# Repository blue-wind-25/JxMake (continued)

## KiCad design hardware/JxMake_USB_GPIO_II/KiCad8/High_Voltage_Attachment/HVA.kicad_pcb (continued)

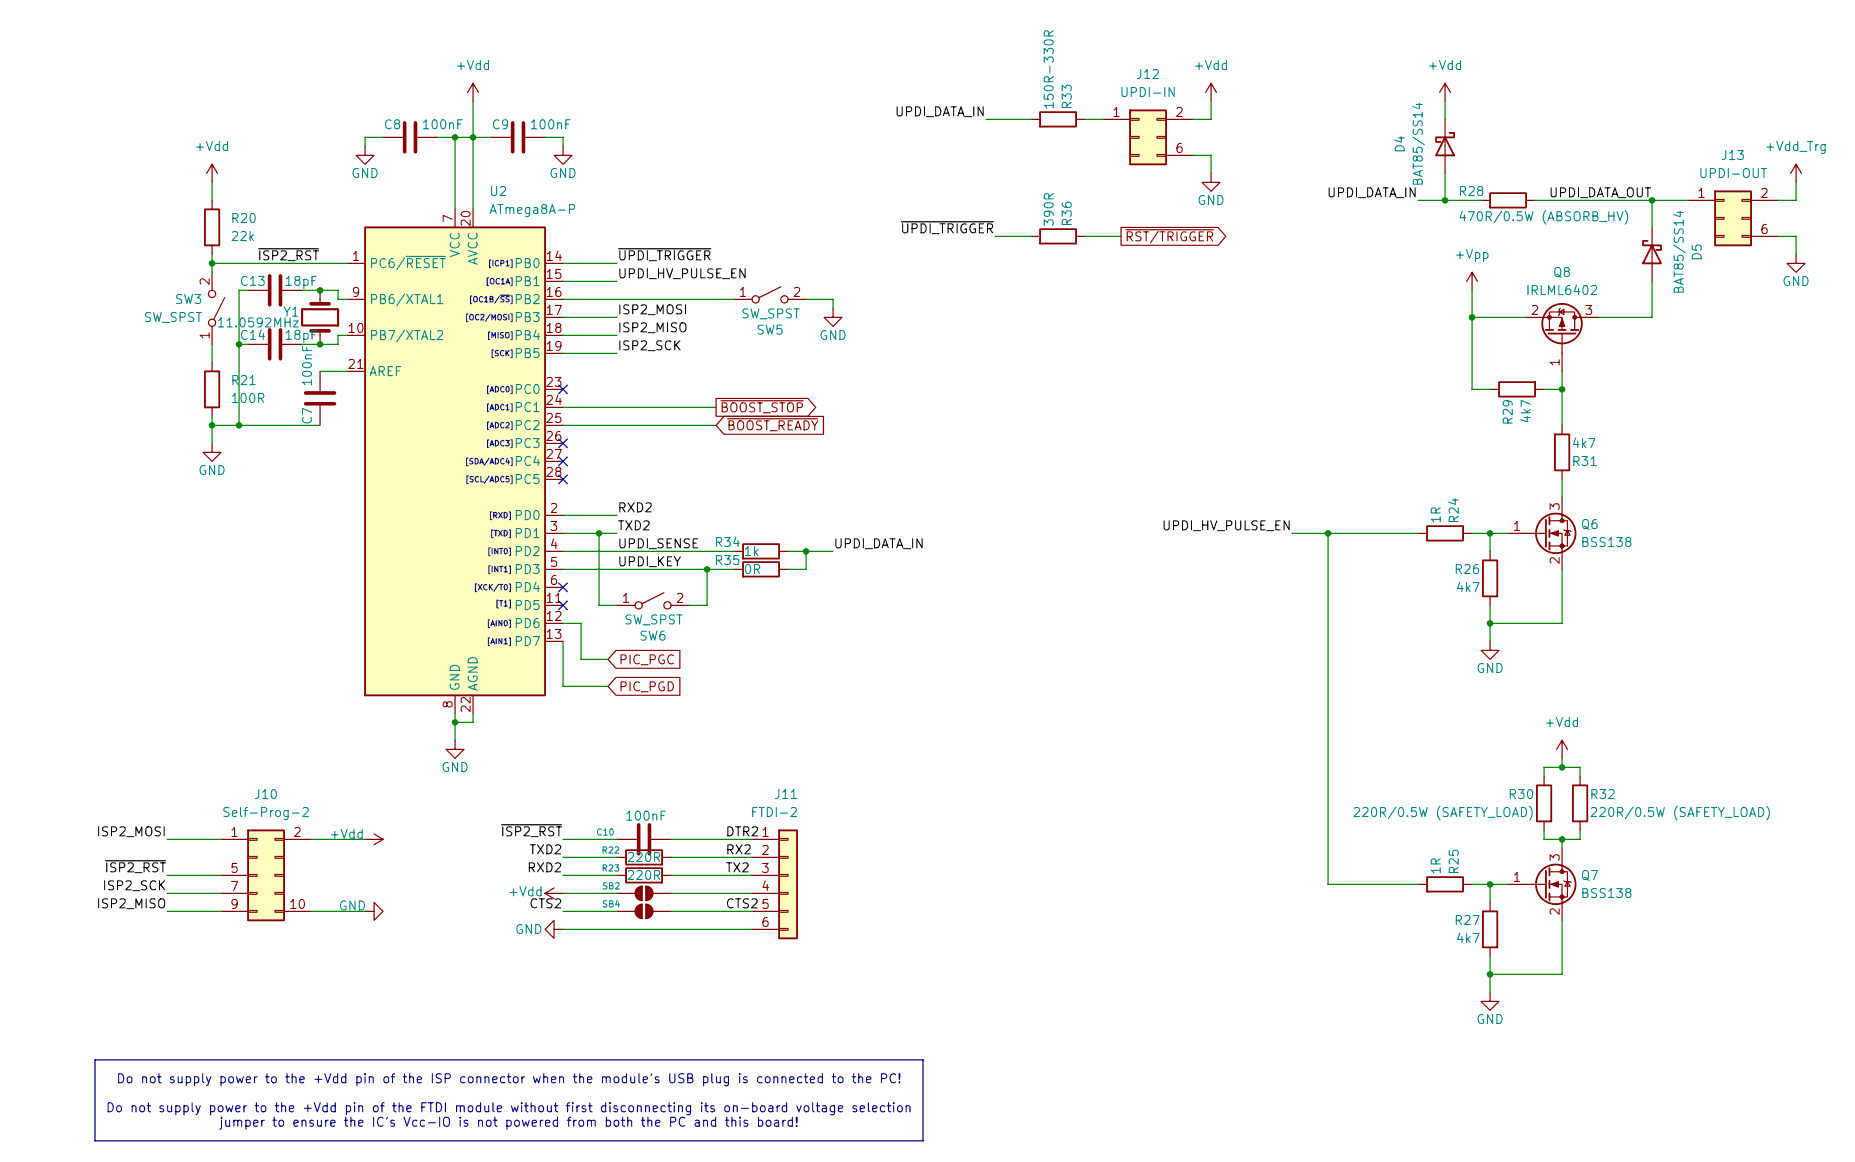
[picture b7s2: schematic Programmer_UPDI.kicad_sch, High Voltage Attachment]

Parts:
C7, C8, C9, C10: 100nF; C_0805_2012Metric_Pad1.18x1.45mm_HandSolder
C13, C14: 18pF; C_0805_2012Metric_Pad1.18x1.45mm_HandSolder
D4, D5: BAT85/SS14; D_SMA
J10: Self-Prog-2; IDC-Header_2x05_P2.54mm_Vertical
J11: FTDI-2; PinSocket_1x06_P2.54mm_Horizontal
J12: UPDI-IN; IDC-Header_2x03_P2.54mm_Vertical
J13: UPDI-OUT; IDC-Header_2x03_P2.54mm_Vertical
Q6, Q7: BSS138; SOT-23_Handsoldering
Q8: IRLML6402; SOT-23_Handsoldering
R20: 22k; R_0805_2012Metric_Pad1.20x1.40mm_HandSolder
R21: 100R; R_0805_2012Metric_Pad1.20x1.40mm_HandSolder
R22, R23: 220R; R_0805_2012Metric_Pad1.20x1.40mm_HandSolder
R24, R25: 1R; R_0805_2012Metric_Pad1.20x1.40mm_HandSolder
R26, R27, R29, R31: 4k7; R_0805_2012Metric_Pad1.20x1.40mm_HandSolder
R28: 470R/0.5W (ABSORB_HV); R_Axial_DIN0207_L6.3mm_D2.5mm_P10.16mm_Horizontal
R30, R32: 220R/0.5W (SAFETY_LOAD); R_Axial_DIN0207_L6.3mm_D2.5mm_P10.16mm_Horizontal
R33: 150R-330R; R_0805_2012Metric_Pad1.20x1.40mm_HandSolder
R34: 1k; R_0805_2012Metric_Pad1.20x1.40mm_HandSolder
R35: 0R; R_0805_2012Metric_Pad1.20x1.40mm_HandSolder
R36: 390R; R_0805_2012Metric_Pad1.20x1.40mm_HandSolder
SB2, SB4: Jumper_2_Small_Bridged; SolderJumper-2_P1.3mm_Open_RoundedPad1.0x1.5mm
SW3, SW5: SW_SPST; SW_SPST_FSMSM
SW6: SW_SPST; PinHeader_1x02_P2.54mm_Vertical
U2: ATmega8A-P; DIP-28_W7.62mm
Y1: 11.0592MHz; Crystal_SMD_HC49-SD

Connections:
+Vdd: C8.2, C9.1, D4.1 (K), J10.2, J12.2, R20.1, R30.1, R32.1, SB2.1 (A), U2.7 (VCC), U2.20 (AVCC); also elsewhere on the board
+Vdd_Trg: J13.2; also elsewhere on the board
+Vpp: Q8.2 (S), R29.1; also elsewhere on the board
/Programmer_UPDI/CTS2: J11.5, SB4.1 (A), SB4.2 (B)
/Programmer_UPDI/DTR2: C10.2, J11.1
/Programmer_UPDI/ISP2_MISO: J10.9, U2.18 (PB4)
/Programmer_UPDI/ISP2_MOSI: J10.1, U2.17 (PB3)
/Programmer_UPDI/ISP2_SCK: J10.7, U2.19 (PB5)
/Programmer_UPDI/RX2: J11.2, R22.2
/Programmer_UPDI/RXD2: R23.1, U2.2 (PD0)
/Programmer_UPDI/TX2: J11.3, R23.2
/Programmer_UPDI/TXD2: R22.1, SW6.1 (A), U2.3 (PD1)
/Programmer_UPDI/UPDI_DATA_IN: D4.2 (A), R28.2, R33.2, R34.1, R35.1
/Programmer_UPDI/UPDI_DATA_OUT: D5.1 (K), J13.1, R28.1
/Programmer_UPDI/UPDI_HV_PULSE_EN: R24.2, R25.2, U2.15 (PB1)
/Programmer_UPDI/UPDI_KEY: R35.2, SW6.2 (B), U2.5 (PD3)
/Programmer_UPDI/UPDI_SENSE: R34.2, U2.4 (PD2)
/Programmer_UPDI/~ISP2_RST: C10.1, J10.5, R20.2, SW3.2 (B), U2.1 (PC6/~RESET)
/Programmer_UPDI/~UPDI_TRIGGER: R36.2, U2.14 (PB0)
GND: C7.1, C8.1, C9.2, C13.1, C14.1, J10.10, J11.6, J12.6, J13.6, Q6.2 (S), Q7.2 (S), R21.2, R26.2, R27.2, SW5.2 (B), U2.8 (GND), U2.22 (AGND); also elsewhere on the board
unnamed: D5.2 (A), Q8.3 (D)
unnamed: J11.4, SB2.2 (B)
unnamed: J12.1, R33.1
unnamed: Q6.3 (D), R31.1
unnamed: Q6.1 (G), R24.1, R26.1
unnamed: Q7.3 (D), R30.2, R32.2
unnamed: Q7.1 (G), R25.1, R27.1
unnamed: Q8.1 (G), R29.2, R31.2
unnamed: R21.1, SW3.1 (A)
unnamed: SW5.1 (A), U2.16 (PB2)
unnamed: C7.2, U2.21 (AREF)
unnamed: C13.2, U2.9 (PB6/XTAL1), Y1.2
unnamed: C14.2, U2.10 (PB7/XTAL2), Y1.1
PIC_PGC: U2.12 (PD6); also elsewhere on the board
PIC_PGD: U2.13 (PD7); also elsewhere on the board
~BOOST_READY: U2.25 (PC2); also elsewhere on the board
~BOOST_STOP: U2.24 (PC1); also elsewhere on the board
~RST/TRIGGER: R36.1; also elsewhere on the board

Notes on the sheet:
Do not supply power to the +Vdd pin of the ISP connector when the module's USB plug is connected to the PC! Do not supply power to the +Vdd pin of the FTDI module without first disconnecting its on-board voltage selection jumper to ensure the IC's Vcc-IO is not powered from both the PC and this boa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
[OC2/MOSI]
[SCL/ADC5]
[XCK/T0]
[INT0]
[ADC1]
[T1]
[RXD]
[ADC2]
[AIN1]
[INT1]
[AIN0]
[TXD]
[MISO]
[SCK]
[ADC0]
[SDA/ADC4]
[ICP1]
[OC1B/~{SS}]
[OC1A]
[ADC3]

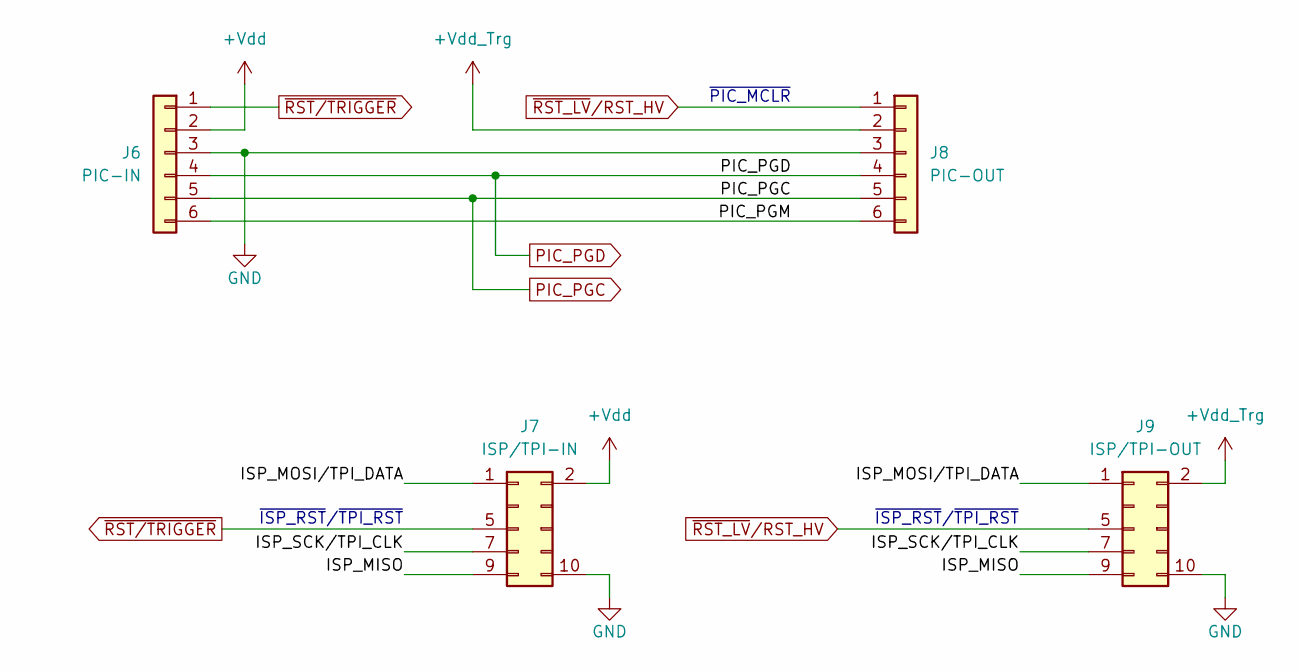
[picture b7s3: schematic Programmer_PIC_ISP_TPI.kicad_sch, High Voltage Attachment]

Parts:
J6: PIC-IN; PinSocket_1x06_P2.54mm_Horizontal
J7: ISP/TPI-IN; IDC-Header_2x05_P2.54mm_Vertical
J8: PIC-OUT; PinSocket_1x06_P2.54mm_Horizontal
J9: ISP/TPI-OUT; IDC-Header_2x05_P2.54mm_Vertical

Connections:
+Vdd: J6.2, J7.2; also elsewhere on the board
+Vdd_Trg: J8.2, J9.2; also elsewhere on the board
/Programmer_PIC_ISP_TPI/ISP_MISO: J7.9, J9.9
/Programmer_PIC_ISP_TPI/ISP_MOSI/TPI_DATA: J7.1, J9.1
/Programmer_PIC_ISP_TPI/ISP_SCK/TPI_CLK: J7.7, J9.7
/Programmer_PIC_ISP_TPI/PIC_PGM: J6.6, J8.6
GND: J6.3, J7.10, J8.3, J9.10; also elsewhere on the board
PIC_PGC: J6.5, J8.5; also elsewhere on the board
PIC_PGD: J6.4, J8.4; also elsewhere on the board
~RST_LV/RST_HV: J8.1, J9.5; also elsewhere on the board
~RST/TRIGGER: J6.1, J7.5; also elsewhere on the board

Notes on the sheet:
~{ISP_RST}/~{TPI_RST}
~{PIC_MCLR}

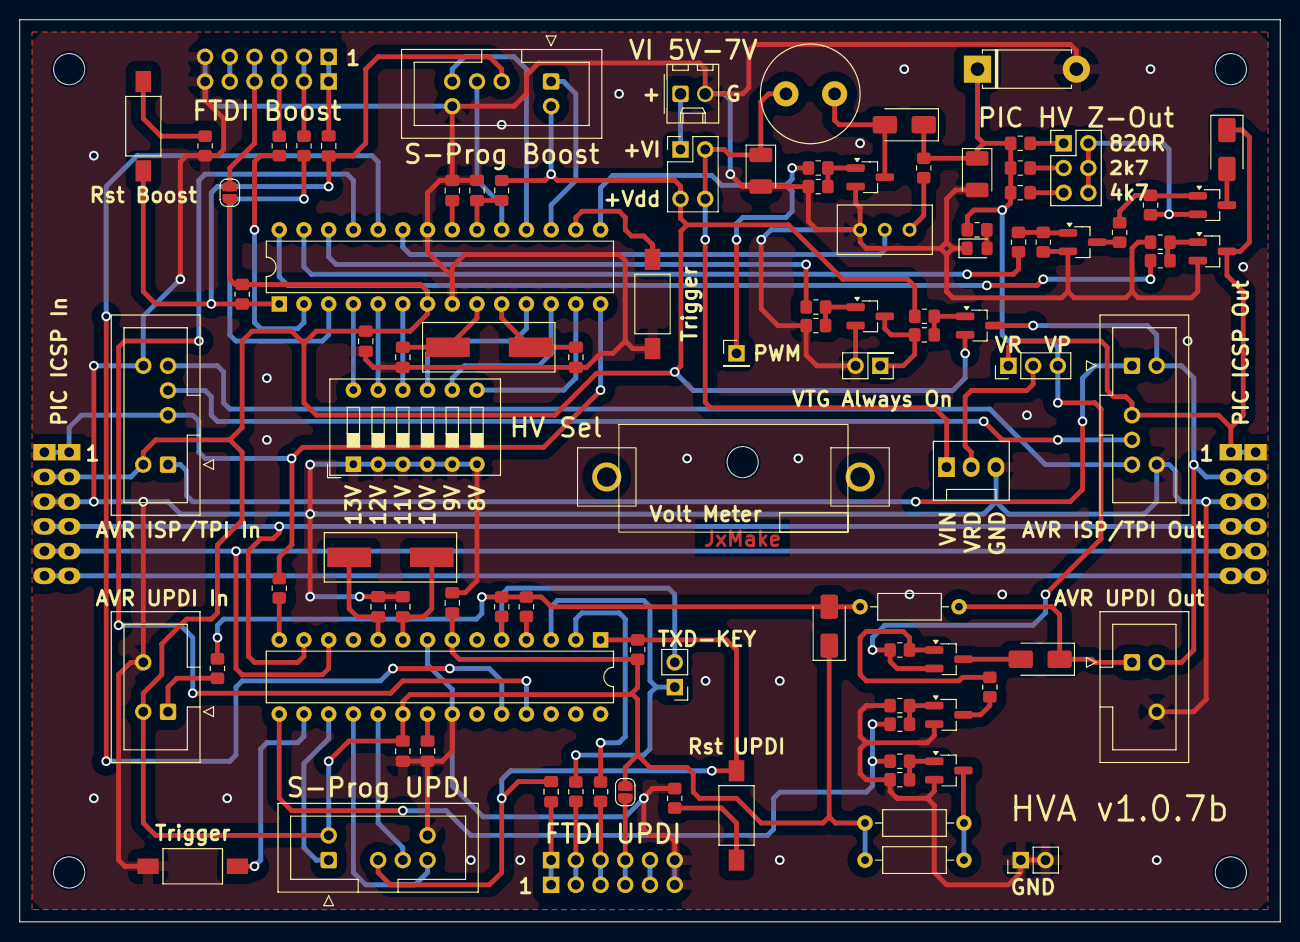
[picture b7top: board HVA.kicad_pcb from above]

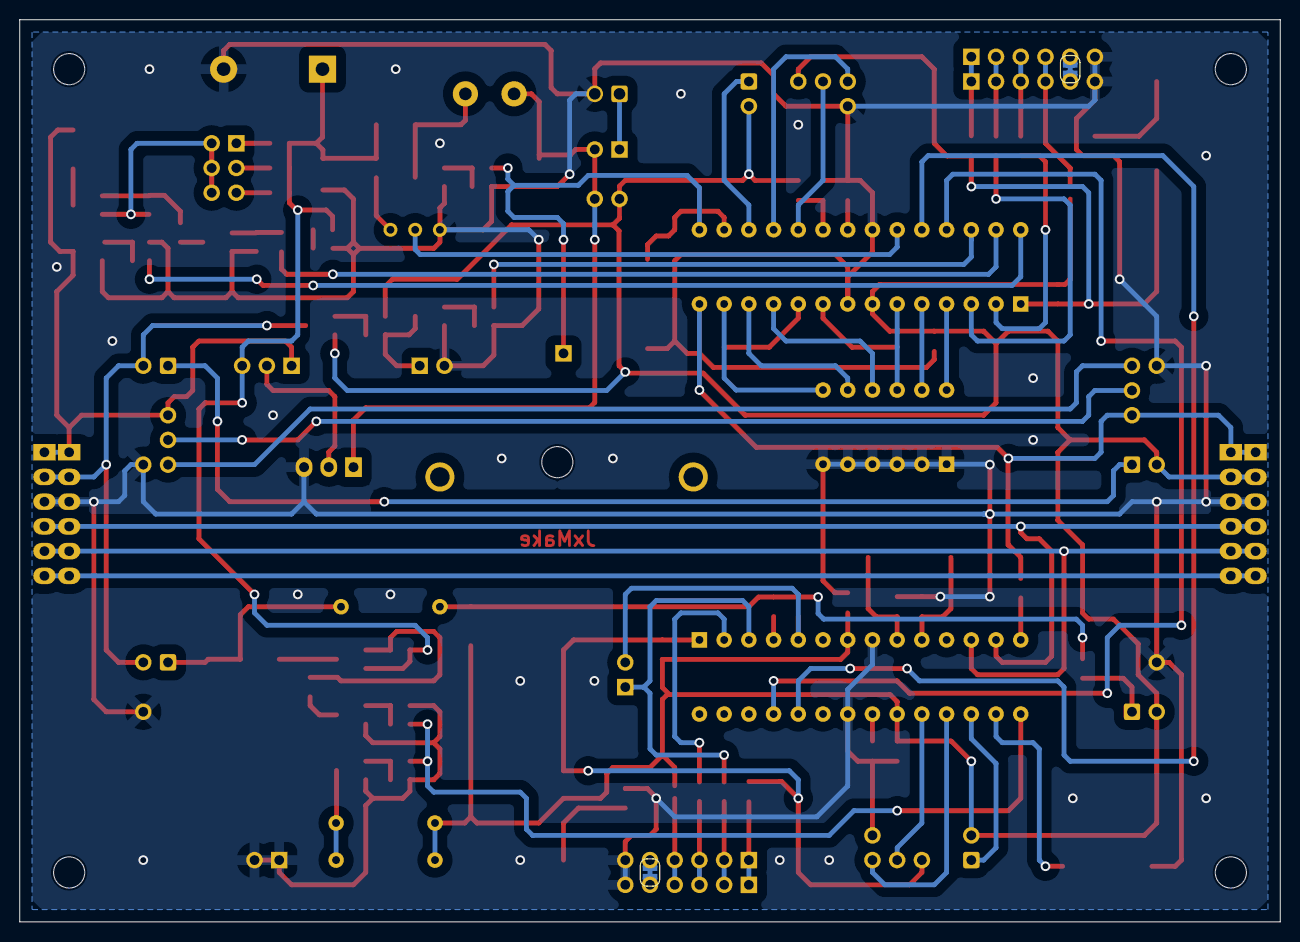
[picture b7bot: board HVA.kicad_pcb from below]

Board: 2 copper layers, 129.5 x 92.7 mm, 107 parts (2 on the bottom side), 90 nets.

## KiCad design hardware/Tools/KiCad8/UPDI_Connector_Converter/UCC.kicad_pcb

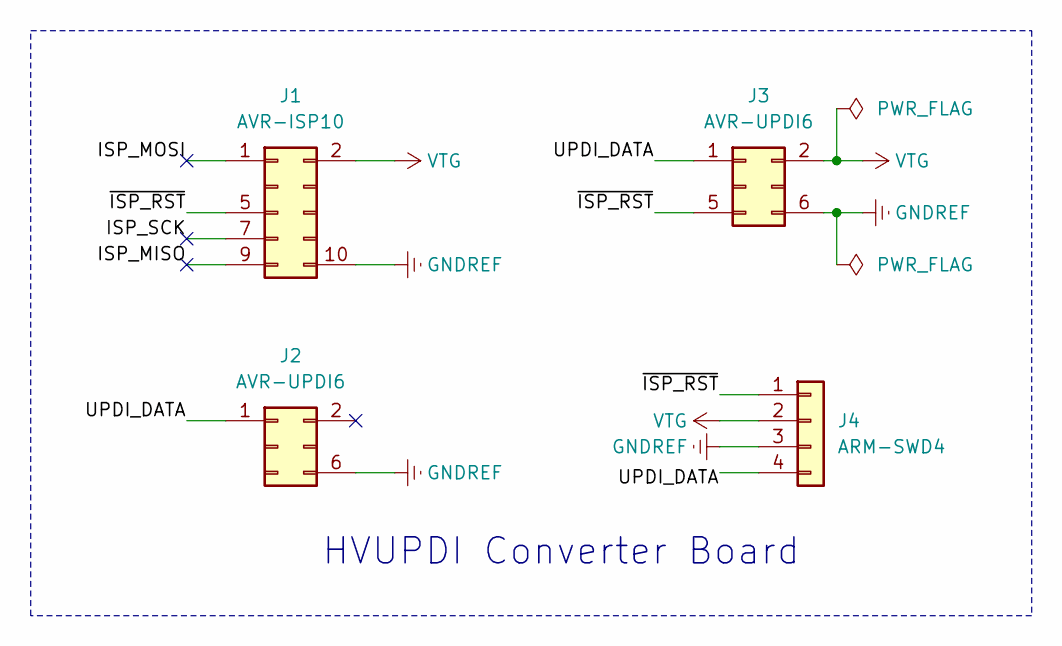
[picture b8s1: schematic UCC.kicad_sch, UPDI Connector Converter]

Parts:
J1: AVR-ISP10; IDC-Header_2x05_P2.54mm_Vertical
J2, J3: AVR-UPDI6; IDC-Header_2x03_P2.54mm_Vertical
J4: ARM-SWD4; PinSocket_1x04_P2.54mm_Horizontal

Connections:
/ISP_MISO: J1.9
/ISP_MOSI: J1.1
/ISP_SCK: J1.7
/UPDI_DATA: J2.1, J3.1, J4.4
/~ISP_RST: J1.5, J3.5, J4.1
GNDREF: J1.10, J2.6, J3.6, J4.3
VTG: J1.2, J3.2, J4.2

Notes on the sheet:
HVUPDI Converter Board

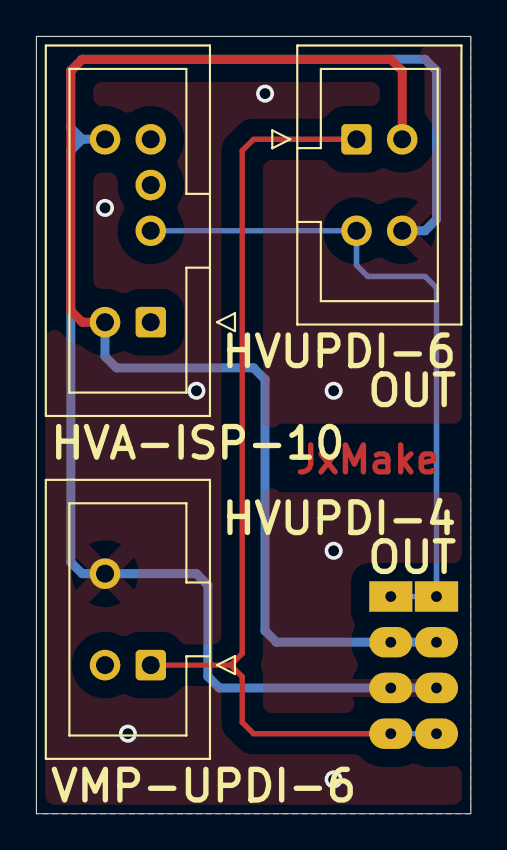
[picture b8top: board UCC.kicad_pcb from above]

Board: 2 copper layers, 24.1 x 43.2 mm, 4 parts (1 on the bottom side), 4 nets.

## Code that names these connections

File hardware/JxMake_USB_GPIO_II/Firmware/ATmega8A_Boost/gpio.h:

/*
 * Copyright (C) 2022-2026 Aloysius Indrayanto
 *
 * This file is part of the JxMake program, see LICENSE file for the license details.
 */


// The pin used to monitor the nRST signal from upstream
#define RST_DDR           DDRB
#define RST_PORT          PORTB
#define RST_PIN           PINB
#define RST_BIT           PB0   // Active low

// The pin used to read the nTRIGGER button
#define TRI_DDR           DDRB
#define TRI_PORT          PORTB
#define TRI_PIN           PINB
#define TRI_BIT           PB2   // Active low

// The pins used to control the target's power and reset
#define TRG_DDR           DDRC
#define TRG_PORT          PORTC
#define TRG_PIN           PINC
#define TRG_BIT_EN_VDD    PC3   // Active high
#define TRG_BIT_RST_HV    PC4   // ---
#define TRG_BIT_RST_LV    PC5   // ---

// The pins used to read the values of the DIP switch
#define DIP_DDR           DDRD
#define DIP_PORT          PORTD
#define DIP_PIN           PIND
#define DIP_BIT_13V       PD2   // Active low
#define DIP_BIT_12V       PD3   // ---
#define DIP_BIT_11V       PD4   // ---
#define DIP_BIT_10V       PD5   // ---
#define DIP_BIT_09V       PD6   // ---
#define DIP_BIT_08V       PD7   // ---
#define DIP_BIT_MASK      0xFC  // 0b11111100

// Pins designated for additional signaling between this section and the 'AVR-UPDI Section'
#define SPC_DDR           DDRC
#define SPC_PORT          PORTC
#define SPC_PIN           PINC
#define SPC_BIT_STOP      PC1   // Active low
#define SPC_BIT_READY     PC2   // Active low


// Initialize GPIOs
static inline void gpioInit()
{
	// Configure the pin used to monitor the nRST signal from upstream as an input with pull-up
	RST_DDR  &= ~_BV(RST_BIT);
	RST_PORT |=  _BV(RST_BIT);

	// Configure the pin used to read the nTRIGGER button as an input with pull-up
	TRI_DDR  &= ~_BV(TRI_BIT);
	TRI_PORT |=  _BV(TRI_BIT);

	// Configure the pins used to control the target's power and reset as outputs
	// and set them to their inactive states
	TRG_PORT &= ~( _BV(TRG_BIT_EN_VDD) | _BV(TRG_BIT_RST_HV) | _BV(TRG_BIT_RST_LV) );
	TRG_DDR  |=  ( _BV(TRG_BIT_EN_VDD) | _BV(TRG_BIT_RST_HV) | _BV(TRG_BIT_RST_LV) );

	// Configure the pins used to read the values of the DIP switch as inputs with pull-ups
	DIP_DDR  &= ~( _BV(DIP_BIT_13V) | _BV(DIP_BIT_12V) | _BV(DIP_BIT_11V) | _BV(DIP_BIT_10V) | _BV(DIP_BIT_09V) | _BV(DIP_BIT_08V) );
	DIP_PORT |=  ( _BV(DIP_BIT_13V) | _BV(DIP_BIT_12V) | _BV(DIP_BIT_11V) | _BV(DIP_BIT_10V) | _BV(DIP_BIT_09V) | _BV(DIP_BIT_08V) );

	// Configure the pins for signaling between this section and the 'AVR-UPDI Section'
	SPC_DDR  &= ~_BV(SPC_BIT_STOP ); // Input with pull-up
	SPC_PORT |=  _BV(SPC_BIT_STOP ); // ---

	SPC_PORT |=  _BV(SPC_BIT_READY); // Output in inactive state
	SPC_DDR  |=  _BV(SPC_BIT_READY); // ---
}


// Read and write GPIOs
static __force_inline bool __gget_loWithDebouncing(volatile uint8_t* pinX, uint8_t bitMask)
{
	if( ( *pinX & bitMask ) != 0 ) return false;

	delayMS(SW_DEBOUNCE_DELAY_MS);

	if( ( *pinX & bitMask ) != 0 ) return false;

	while( ( *pinX & bitMask ) == 0 ) wdt_reset();

	return true;
}

static __force_inline bool    gget_nRST          () { return ( RST_PIN & _BV(RST_BIT) ) == 0; }

static __force_inline bool    gget_nTRIGGER      () { return __gget_loWithDebouncing( &TRI_PIN, _BV(TRI_BIT) ); }

static __force_inline void    gset_trgEnaVdd     () { TRG_PORT |=  _BV(TRG_BIT_EN_VDD); }
static __force_inline void    gset_trgDisVdd     () { TRG_PORT &= ~_BV(TRG_BIT_EN_VDD); }

static __force_inline void    gset_trgEnaRstHV   () { TRG_PORT |=  _BV(TRG_BIT_RST_HV); }
static __force_inline void    gset_trgDisRstHV   () { TRG_PORT &= ~_BV(TRG_BIT_RST_HV); }

static __force_inline void    gset_trgEnaRstLV   () { TRG_PORT |=  _BV(TRG_BIT_RST_LV); }
static __force_inline void    gset_trgDisRstLV   () { TRG_PORT &= ~_BV(TRG_BIT_RST_LV); }

static __force_inline uint8_t gget_dipAll        () { return   DIP_PIN & DIP_BIT_MASK           ; }
static __force_inline bool    gget_dipn13V       () { return ( DIP_PIN & _BV(DIP_BIT_13V) ) == 0; }
static __force_inline bool    gget_dipn12V       () { return ( DIP_PIN & _BV(DIP_BIT_12V) ) == 0; }
static __force_inline bool    gget_dipn11V       () { return ( DIP_PIN & _BV(DIP_BIT_11V) ) == 0; }
static __force_inline bool    gget_dipn10V       () { return ( DIP_PIN & _BV(DIP_BIT_10V) ) == 0; }
static __force_inline bool    gget_dipn09V       () { return ( DIP_PIN & _BV(DIP_BIT_09V) ) == 0; }
static __force_inline bool    gget_dipn08V       () { return ( DIP_PIN & _BV(DIP_BIT_08V) ) == 0; }

static __force_inline bool    gget_nBoostStop    () { return ( SPC_PIN & _BV(SPC_BIT_STOP) ) == 0; }
static __force_inline void    gset_nBoostReady   () { SPC_PORT &=  ~_BV(SPC_BIT_READY);            }
static __force_inline void    gset_nBoostNotReady() { SPC_PORT |=   _BV(SPC_BIT_READY);            }

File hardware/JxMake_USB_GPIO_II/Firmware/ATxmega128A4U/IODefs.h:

/*
 * Copyright (C) 2022-2026 Aloysius Indrayanto
 *
 * This file is part of the JxMake program, see LICENSE file for the license details.
 */


#ifndef __IO_DEFS_H__
#define __IO_DEFS_H__


// DMA channel assigment
#define DEBUG_UART_DMA      DMA.CH3
#define DEBUG_UART_DMA_TRIG DMA_CH_TRIGSRC_USARTE0_DRE_gc

#define HW_UXRT_DMA         DMA.CH2
#define HW_UXRT_DMA_TRIG    DMA_CH_TRIGSRC_USARTD0_DRE_gc



// Debugging UART
#define DEBUG_UART          USARTE0
#define DEBUG_UART_PORT     E
#define DEBUG_UART_RX_BIT   2 // RXD0 -> PE.2
#define DEBUG_UART_TX_BIT   3 // TXD0 -> PE.3


// ADC pin for VREAD
#define ADC_VREAD_CHANNEL   ADC_CH_MUXPOS_PIN8_gc
#define ADC_VREAD_PORT      B
#define ADC_VREAD_BIT       0


// Control pins used by 'Versatile MCU Programmer'
#define NCTL0_PORT          B
#define NCTL0_BIT           1 // nCTL0 -> PB.1 : XCK→  nSS→  SCK→

#define CTL0_PORT           B
#define CTL0_BIT            2 //  CTL0 -> PB.2 : RXD0← MISO←      ; NOTE : These two pins are always in input mode.

#define CTL1_PORT           B
#define CTL1_BIT            3 //  CTL1 -> PB.3 : TXD0→

#define CTL2_PORT           D
#define CTL2_BIT            0 //  CTL2 -> PD.0 :       MOSI→


// HW-SPI
#define HW_SPI_SPI          SPIC
#define HW_SPI_PORT         C

#define HW_SPI_NSS_BIT      4 // nSS  -> PC.4
#define HW_SPI_SCK_BIT      7 // SCK  -> PC.7
#define HW_SPI_MOSI_BIT     5 // MOSI -> PC.5
#define HW_SPI_MISO_BIT     6 // MISO -> PC.6

#define HW_SPI_VPORT        VPORT0
#define HW_SPI_VPORTCFG()   do { PORTCFG.VPCTRLA = (PORTCFG.VPCTRLA & ~PORTCFG_VP0MAP_gm) | (PORTCFG_VP02MAP_PORTC_gc << PORTCFG_VP0MAP_gp); } while(0)

#define HW_SPI_NSS_LLT      HW_nSS
#define HW_SPI_SCK_LLT      HW_SCK
#define HW_SPI_MOSI_LLT     HW_MOSI


// HW-TWI
#define TWI_TWI             TWIE
#define TWI_PORT            E
#define TWI_SDA_BIT         0 // SDA -> PE.0
#define TWI_SCL_BIT         1 // SCL -> PE.1


// HW-UXRT
#define HW_UXRT             USARTD0
#define HW_UXRT_ISR_RXC     USARTD0_RXC_vect
#define HW_UXRT_PORT        D
#define HW_UXRT_RXD_BIT     2 // RXD0 -> PD.2
#define HW_UXRT_TXD_BIT     3 // TXD0 -> PD.3
#define HW_UXRT_XCK_BIT     1 // XCK0 -> PD.1

#define HW_UXRT_NSS_PORT    HW_SPI_PORT
#define HW_UXRT_NSS_BIT     HW_SPI_NSS_BIT

#define HW_UXRT_TXD_LLT     HW_TXD
#define HW_UXRT_XCK_LLT     HW_XCK

#define HW_UXRT_NSS_LLT     HW_SPI_NSS_LLT


// BB-USRT
#define BB_USRT_PORT        HW_SPI_PORT

#define BB_USRT_XCK_BIT     HW_SPI_SCK_BIT
#define BB_USRT_TXD_BIT     HW_SPI_MOSI_BIT
#define BB_USRT_RXD_BIT     HW_SPI_MISO_BIT

#define BB_USRT_TXD_LLT     HW_SPI_MOSI_LLT
#define BB_USRT_XCK_LLT     HW_SPI_SCK_LLT


// BB-SWIM
#define BB_SWIM_PORT        HW_SPI_PORT

#define BB_SWIM_SDO_BIT     HW_SPI_MOSI_BIT
#define BB_SWIM_SDI_BIT     HW_SPI_MISO_BIT

#define BB_SWIM_VPORT       HW_SPI_VPORT
#define BB_SWIM_VPORTCFG()  HW_SPI_VPORTCFG()


// BB-JTAG
#define BB_JTAG_M_PORT      HW_SPI_PORT  // TDI TDO TCK nRST
#define BB_JTAG_S_PORT      HW_UXRT_PORT // TMS         nTRST

#define BB_JTAG_S_NTRST_BIT HW_UXRT_XCK_BIT
#define BB_JTAG_M_TDI_BIT   HW_SPI_MOSI_BIT
#define BB_JTAG_S_TMS_BIT   HW_UXRT_TXD_BIT
#define BB_JTAG_M_TCK_BIT   HW_SPI_SCK_BIT
#define BB_JTAG_M_TDO_BIT   HW_SPI_MISO_BIT
#define BB_JTAG_M_NRST_BIT  HW_SPI_NSS_BIT

#define BB_JTAG_S_NTRST_LLT HW_UXRT_XCK_LLT // NOTE : These values should be unused because the code will use SPI and UART
#define BB_JTAG_M_TDI_LLT   HW_SPI_MOSI_LLT //        functions to initialize JTAG
#define BB_JTAG_S_TMS_LLT   HW_UXRT_TXD_LLT // ---
#define BB_JTAG_M_TCK_LLT   HW_SPI_SCK_LLT  // ---
#define BB_JTAG_M_NRST_LLT  HW_SPI_NSS_LLT  // ---


#endif // __IO_DEFS_H__
